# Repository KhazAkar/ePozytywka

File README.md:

# ePozytywka
Odtwarzacz MP3 oparty o STM32F030, wyświetlacz TFT dotykowy i moduł DFPlayer Mini do odtwarzania plików MP3

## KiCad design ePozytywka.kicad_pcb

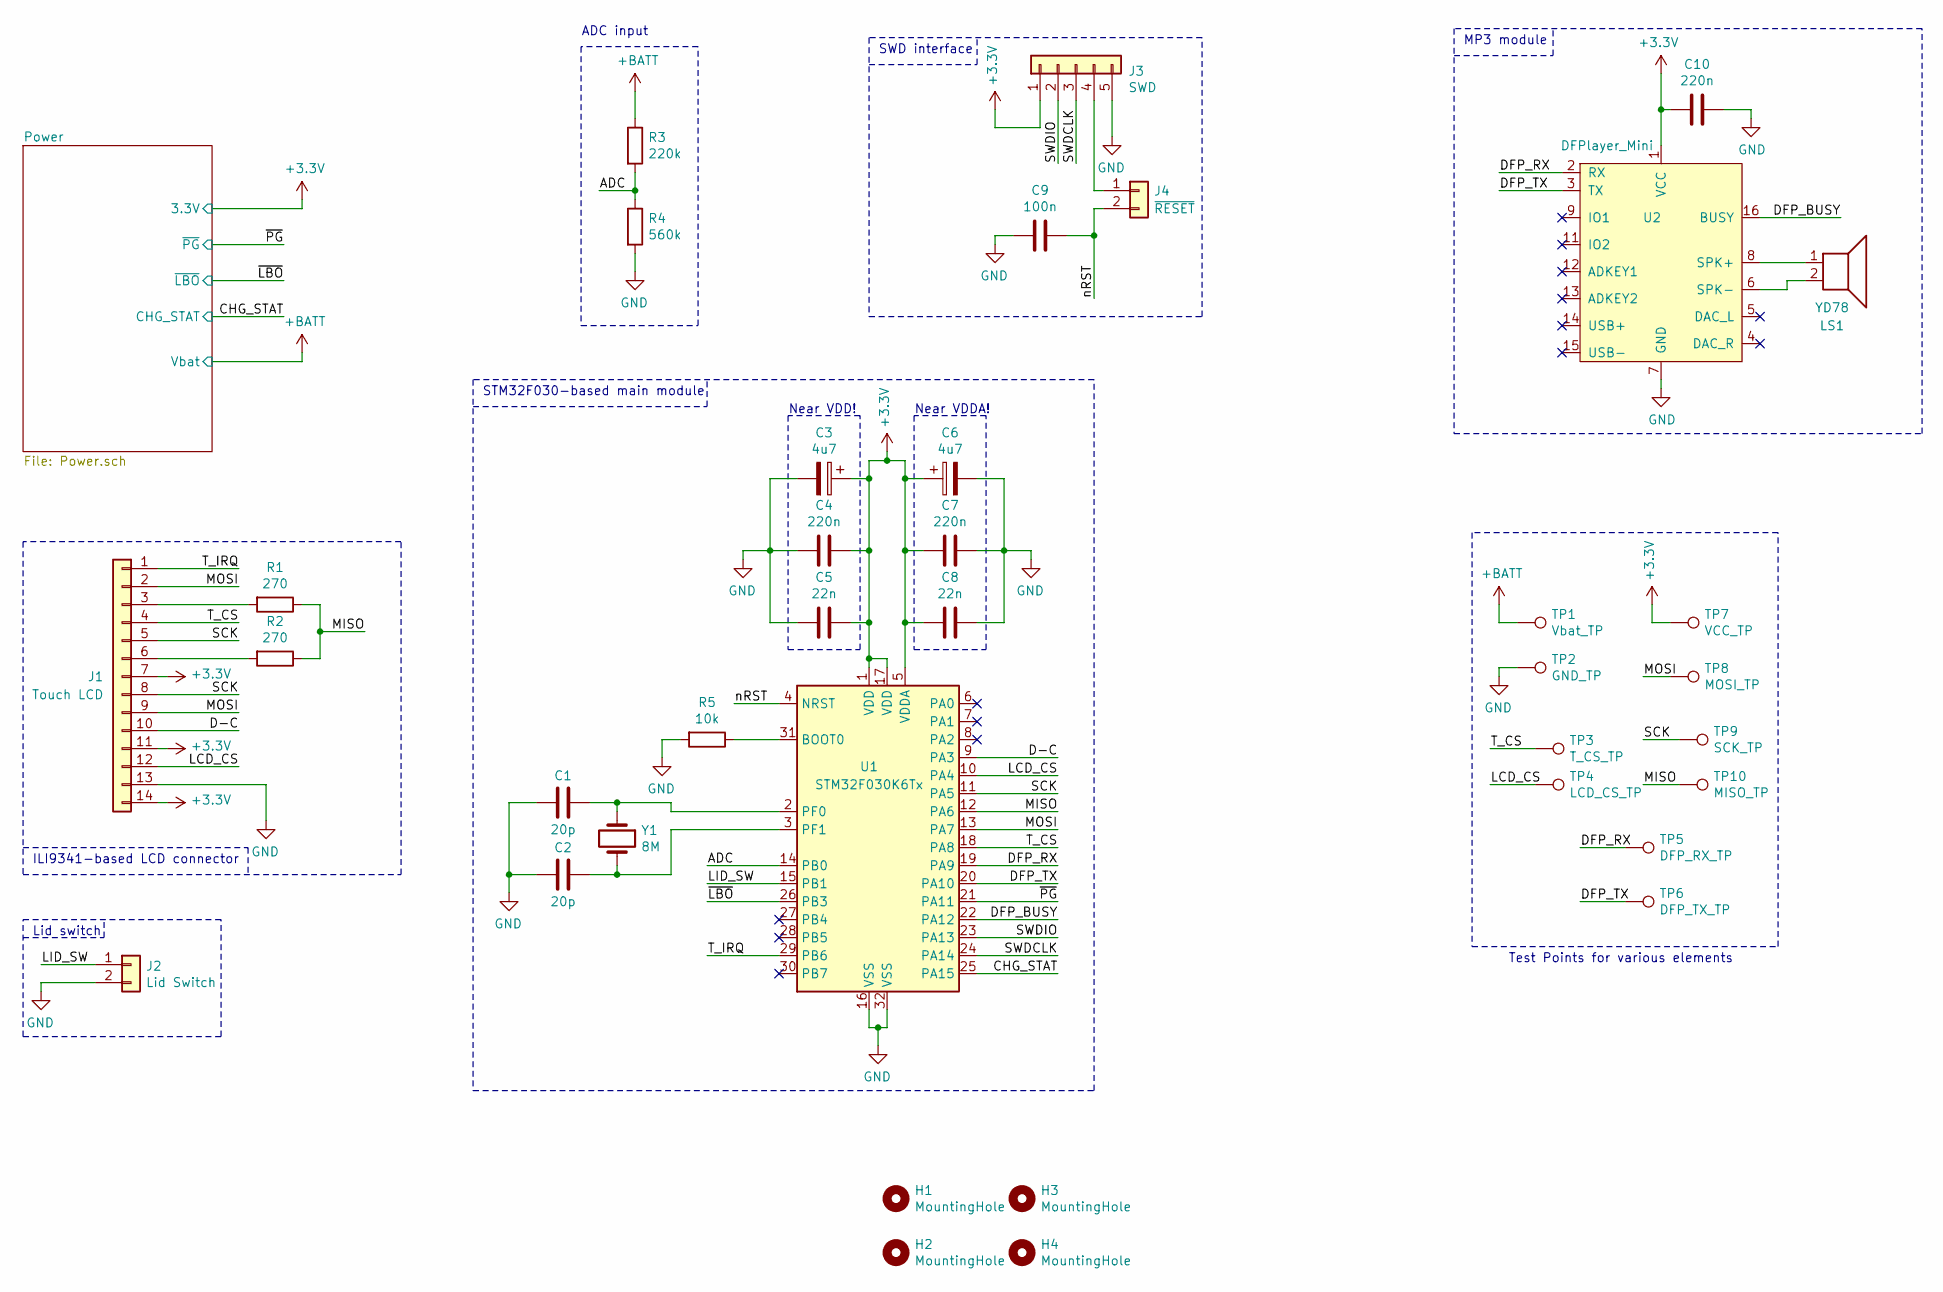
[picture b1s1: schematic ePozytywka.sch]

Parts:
C1, C2: 20p; C_0603_1608Metric_Pad1.05x0.95mm_HandSolder
C3, C6: 4u7; CP_Elec_4x5.3
C4, C7, C10: 220n; C_0603_1608Metric_Pad1.05x0.95mm_HandSolder
C5, C8: 22n; C_0603_1608Metric_Pad1.05x0.95mm_HandSolder
C9: 100n; C_0603_1608Metric_Pad1.05x0.95mm_HandSolder
H1, H2, H3, H4: MountingHole; MountingHole_3.2mm_M3
J1: Touch LCD; PinHeader_1x14_P2.54mm_Vertical
J2: Lid Switch; PinHeader_1x02_P2.54mm_Vertical
J3: SWD; PinHeader_1x05_P2.54mm_Vertical
J4: ~RESET; PinHeader_1x02_P2.54mm_Vertical
LS1: YD78; PinHeader_1x02_P2.54mm_Vertical
R1, R2: 270; R_0603_1608Metric_Pad1.05x0.95mm_HandSolder
R3: 220k; R_0603_1608Metric_Pad1.05x0.95mm_HandSolder
R4: 560k; R_0603_1608Metric_Pad1.05x0.95mm_HandSolder
R5: 10k; R_0603_1608Metric_Pad1.05x0.95mm_HandSolder
TP1: Vbat_TP; TestPoint_Pad_D1.0mm
TP2: GND_TP; TestPoint_Pad_D1.0mm
TP3: T_CS_TP; TestPoint_Pad_D1.0mm
TP4: LCD_CS_TP; TestPoint_Pad_D1.0mm
TP5: DFP_RX_TP; TestPoint_Pad_D1.0mm
TP6: DFP_TX_TP; TestPoint_Pad_D1.0mm
TP7: VCC_TP; TestPoint_Pad_D1.0mm
TP8: MOSI_TP; TestPoint_Pad_D1.0mm
TP9: SCK_TP; TestPoint_Pad_D1.0mm
TP10: MISO_TP; TestPoint_Pad_D1.0mm
U1: STM32F030K6Tx; LQFP-32_7x7mm_P0.8mm
U2: DFPlayer_Mini
Y1: 8M; Crystal_SMD_TXC_7A-2Pin_5x3.2mm

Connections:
+3V3: C3.1, C4.1, C5.2, C6.1, C7.1, C8.1, C10.1, J1.7, J1.11, J1.14, J3.1, TP7.1, U1.1 (VDD), U1.5 (VDDA), U1.17 (VDD), U2.1 (VCC); also elsewhere on the board
+BATT: R3.1, TP1.1; also elsewhere on the board
/ADC: R3.2, R4.1, U1.14 (PB0)
/CHG_STAT: U1.25 (PA15); also elsewhere on the board
/D-C: J1.10, U1.9 (PA3)
/DFP_BUSY: U1.22 (PA12), U2.16 (BUSY)
/DFP_RX: TP5.1, U1.19 (PA9), U2.2 (RX)
/DFP_TX: TP6.1, U1.20 (PA10), U2.3 (TX)
/LCD_CS: J1.12, TP4.1, U1.10 (PA4)
/LID_SW: J2.1, U1.15 (PB1)
/MISO: R1.1, R2.1, TP10.1, U1.12 (PA6)
/MOSI: J1.2, J1.9, TP8.1, U1.13 (PA7)
/SCK: J1.5, J1.8, TP9.1, U1.11 (PA5)
/SWDCLK: J3.3, U1.24 (PA14)
/SWDIO: J3.2, U1.23 (PA13)
/T_CS: J1.4, TP3.1, U1.18 (PA8)
/T_IRQ: J1.1, U1.29 (PB6)
/nRST: C9.2, J4.2, U1.4 (NRST)
/~LBO: U1.26 (PB3); also elsewhere on the board
/~PG: U1.21 (PA11); also elsewhere on the board
GND: C1.2, C2.2, C3.2, C4.2, C5.1, C6.2, C7.2, C8.2, C9.1, C10.2, J1.13, J2.2, J3.5, R4.2, R5.2, TP2.1, U1.16 (VSS), U1.32 (VSS), U2.7 (GND), U2.10 (GND); also elsewhere on the board
unnamed: C1.1, U1.2 (PF0), Y1.1
unnamed: C2.1, U1.3 (PF1), Y1.2
unnamed: J1.3, R1.2
unnamed: J1.6, R2.2
unnamed: J3.4, J4.1
unnamed: LS1.1, U2.8 (SPK+)
unnamed: LS1.2, U2.6 (SPK-)
unnamed: R5.1, U1.31 (BOOT0)

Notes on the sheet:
MP3 module
Near VDDA!
Near VDD!
ILI9341-based LCD connector
Test Points for various elements
Lid switch
STM32F030-based main module
SWD interface
ADC input

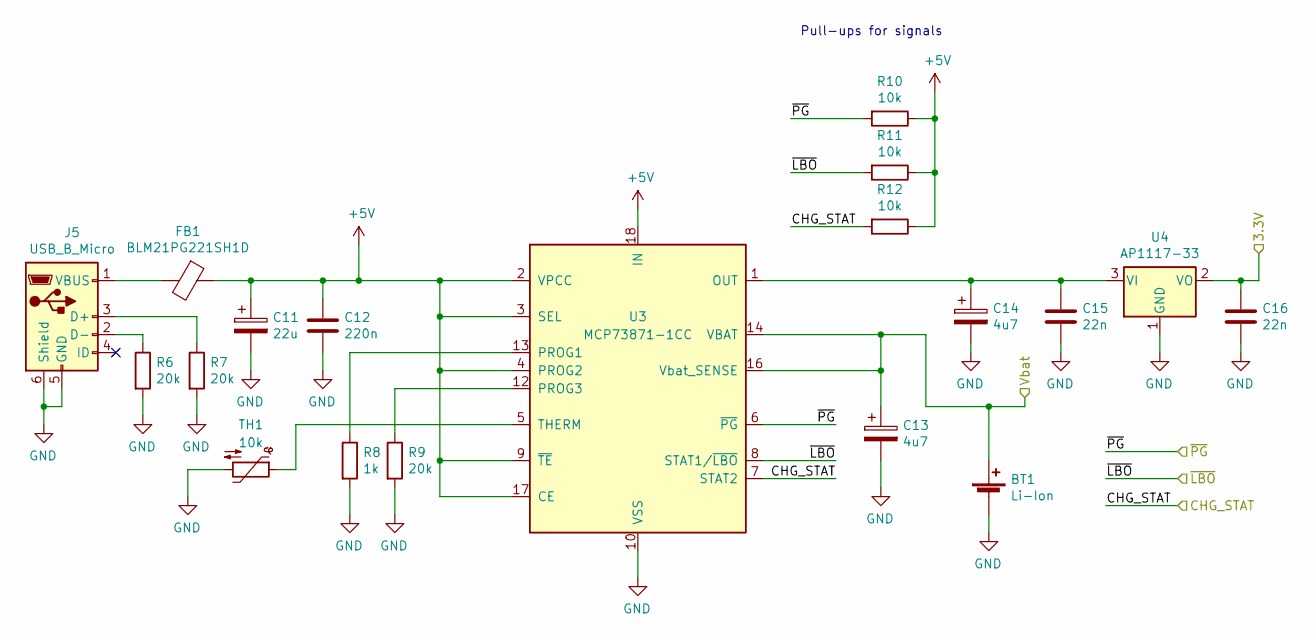
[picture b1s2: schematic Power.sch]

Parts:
BT1: Li-Ion; PinHeader_1x02_P2.54mm_Vertical
C11: 22u; CP_Elec_4x5.3
C12: 220n; C_0603_1608Metric_Pad1.05x0.95mm_HandSolder
C13, C14: 4u7; CP_Elec_4x5.3
C15, C16: 22n; C_0603_1608Metric_Pad1.05x0.95mm_HandSolder
FB1: BLM21PG221SH1D; L_0805_2012Metric_Pad1.15x1.40mm_HandSolder
J5: USB_B_Micro; AMPHENOL_10118192-0001LF
R6, R7, R9: 20k; R_0603_1608Metric_Pad1.05x0.95mm_HandSolder
R8: 1k; R_0603_1608Metric_Pad1.05x0.95mm_HandSolder
R10, R11, R12: 10k; R_0603_1608Metric_Pad1.05x0.95mm_HandSolder
TH1: 10k; PinHeader_1x02_P2.54mm_Vertical
U3: MCP73871-1CC; QFN-20-1EP_4x4mm_P0.5mm_EP2.5x2.5mm
U4: AP1117-33; SOT-223-3_TabPin2

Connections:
+3V3: C16.2, U4.2 (VO); also elsewhere on the board
+5V: C11.1, C12.2, FB1.1, R10.1, R11.1, R12.1, U3.2 (VPCC), U3.3 (SEL), U3.4 (PROG2), U3.9 (~TE), U3.17 (CE), U3.18 (IN), U3.19 (IN)
+BATT: BT1.1 (+), C13.1, U3.14 (VBAT), U3.15 (VBAT), U3.16 (Vbat_SENSE); also elsewhere on the board
/CHG_STAT: R12.2, U3.7 (STAT2); also elsewhere on the board
/~LBO: R11.2, U3.8 (STAT1/~LBO~); also elsewhere on the board
/~PG: R10.2, U3.6 (~PG~); also elsewhere on the board
GND: BT1.2 (-), C11.2, C12.1, C13.2, C14.2, C15.1, C16.1, J5.5 (GND), J5.6 (Shield), R6.2, R7.2, R8.2, R9.2, TH1.2, U3.10 (VSS), U3.11 (VSS), U3.21 (VSS), U4.1 (GND); also elsewhere on the board
unnamed: C14.1, C15.2, U3.1 (OUT), U3.20 (OUT), U4.3 (VI)
unnamed: FB1.2, J5.1 (VBUS)
unnamed: J5.2 (D-), R6.1
unnamed: J5.3 (D+), R7.1
unnamed: R8.1, U3.13 (PROG1)
unnamed: R9.1, U3.12 (PROG3)
unnamed: TH1.1, U3.5 (THERM)

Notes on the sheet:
Pull-ups for signals

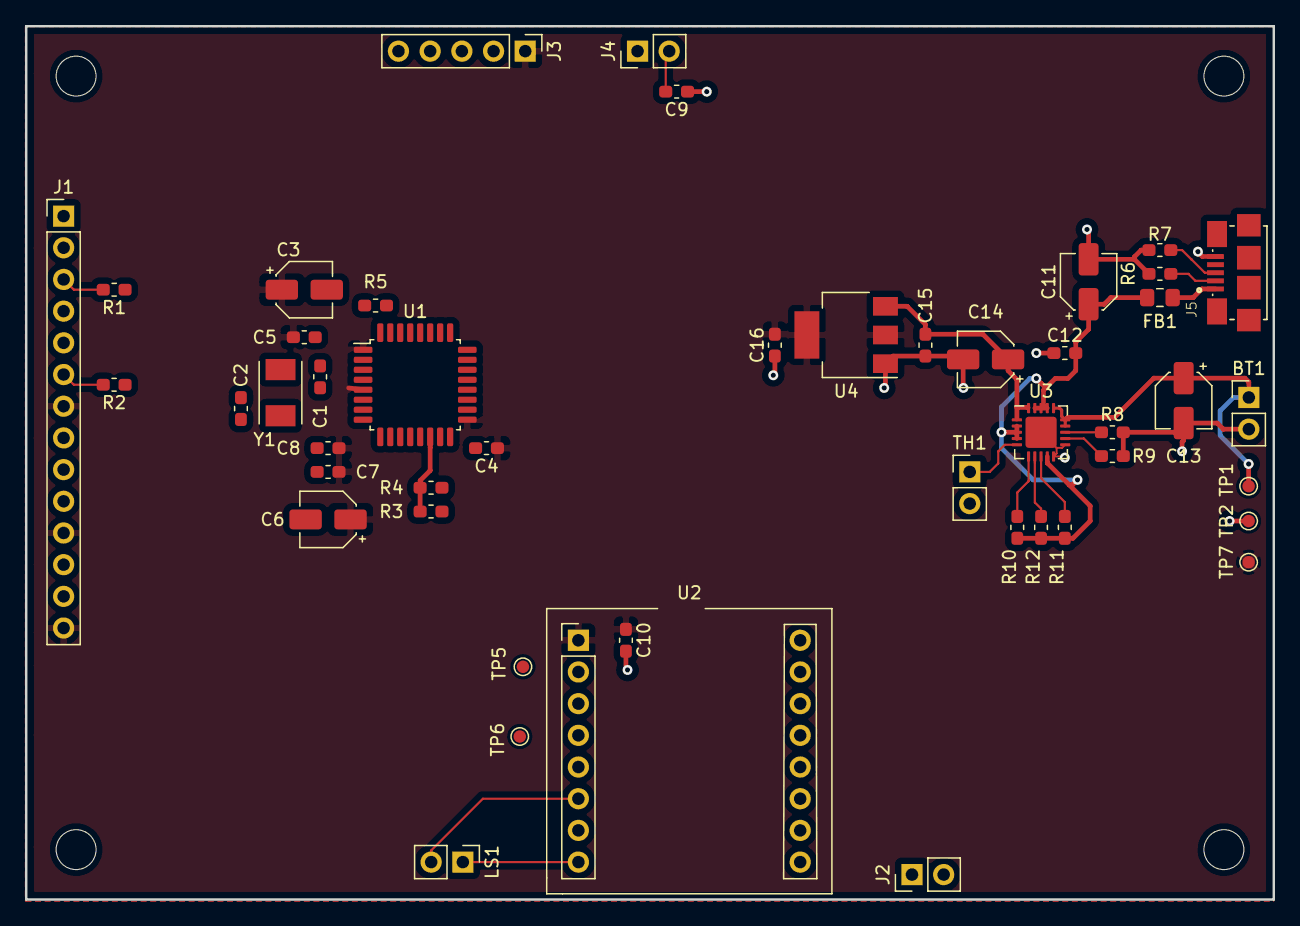
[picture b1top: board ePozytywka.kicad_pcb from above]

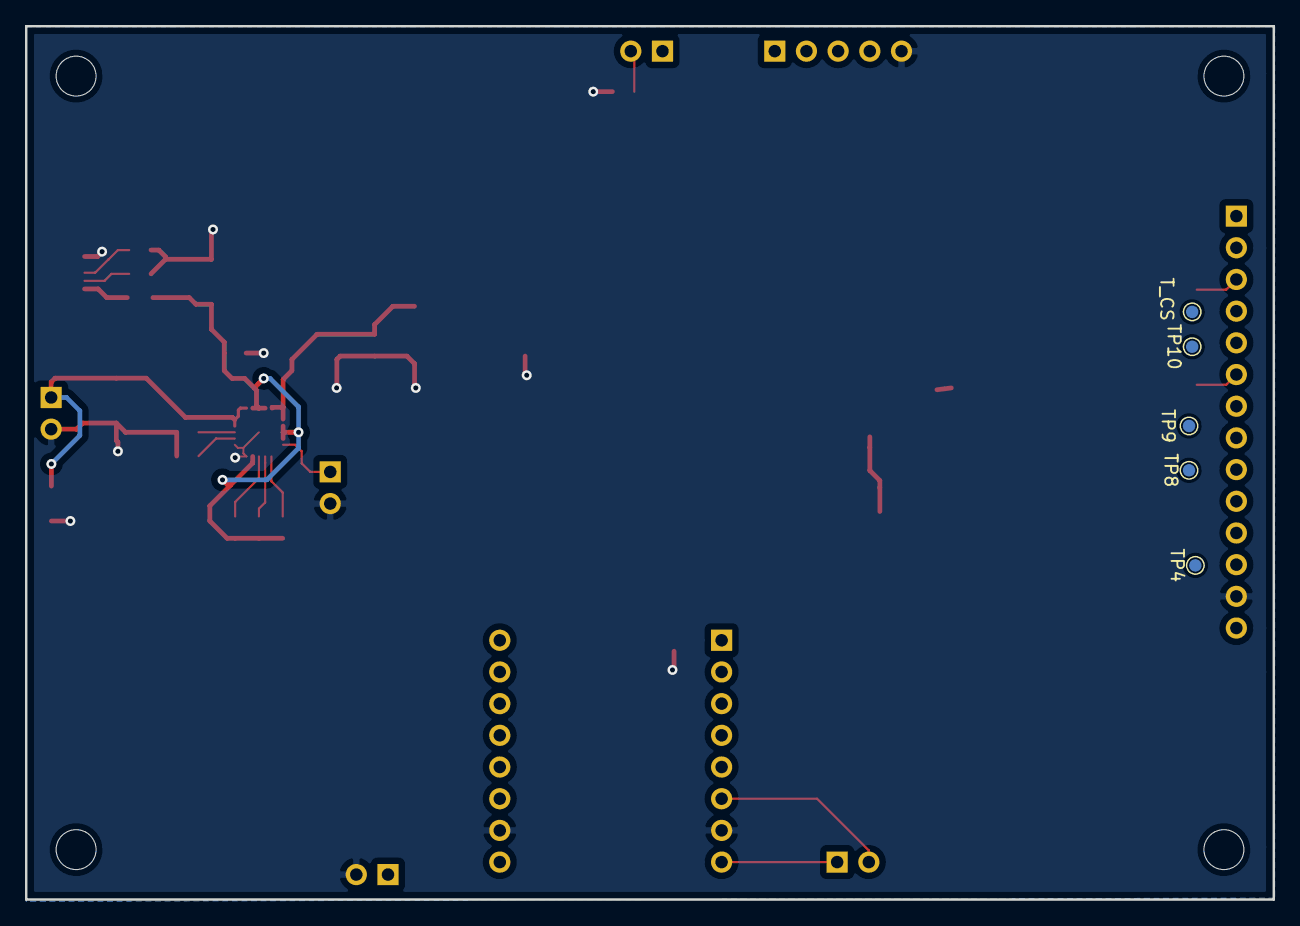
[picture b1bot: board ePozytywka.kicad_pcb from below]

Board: 2 copper layers, 100.0 x 70.0 mm, 56 parts (5 on the bottom side), 37 nets.
